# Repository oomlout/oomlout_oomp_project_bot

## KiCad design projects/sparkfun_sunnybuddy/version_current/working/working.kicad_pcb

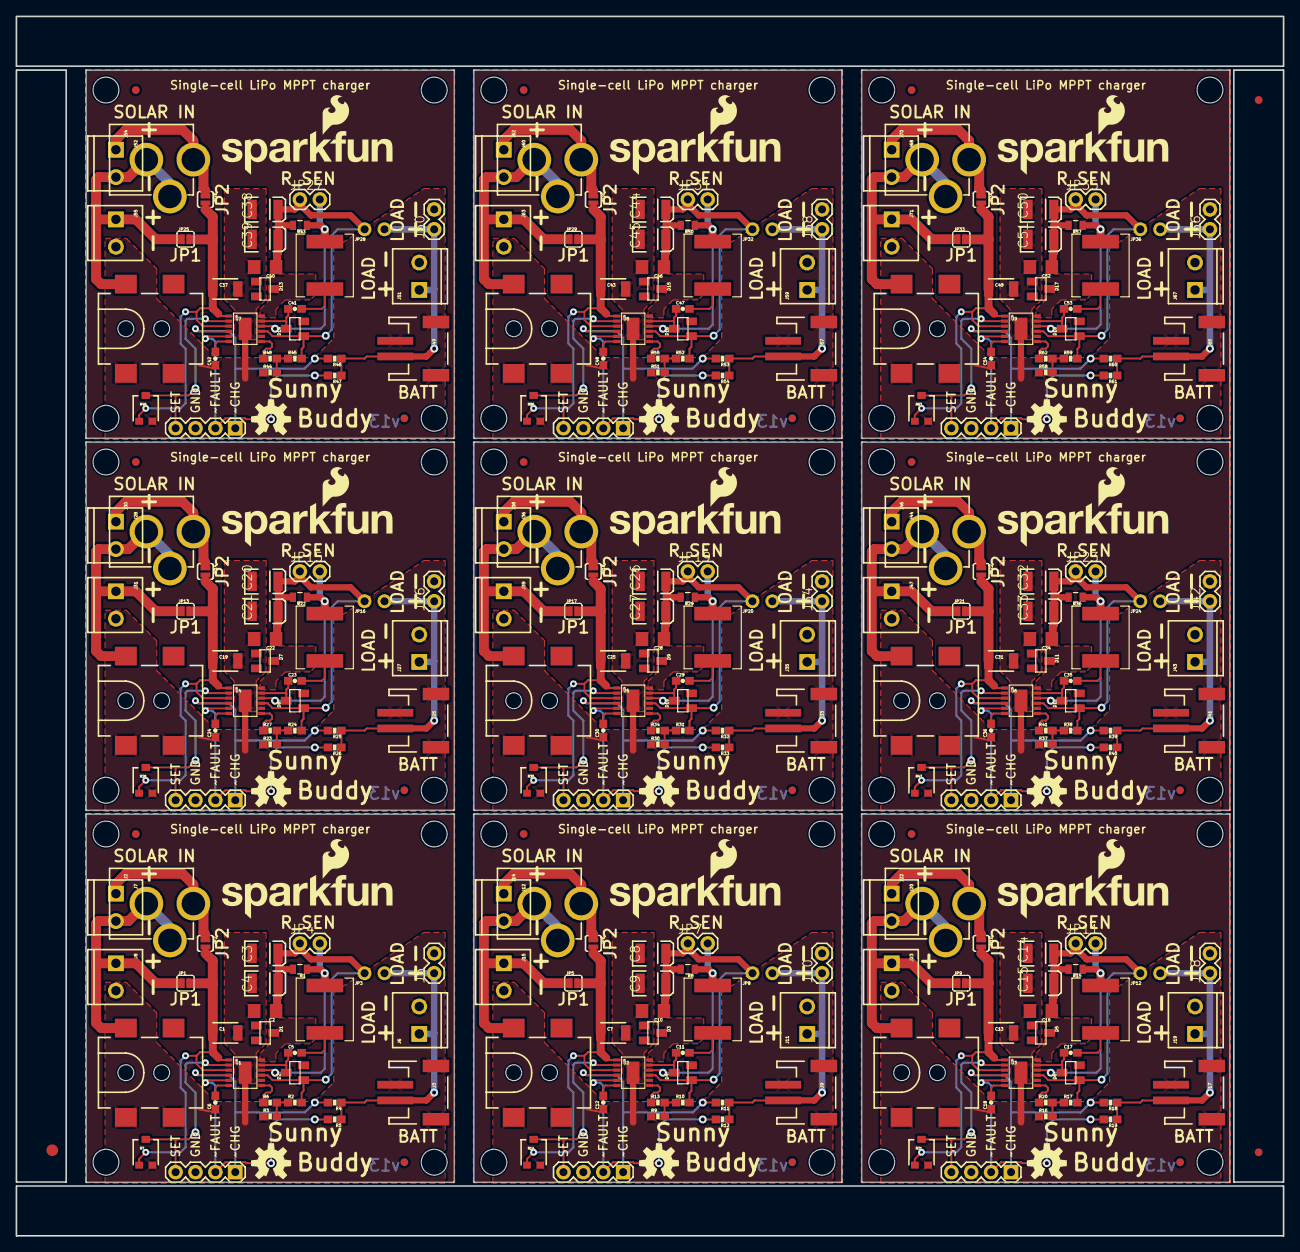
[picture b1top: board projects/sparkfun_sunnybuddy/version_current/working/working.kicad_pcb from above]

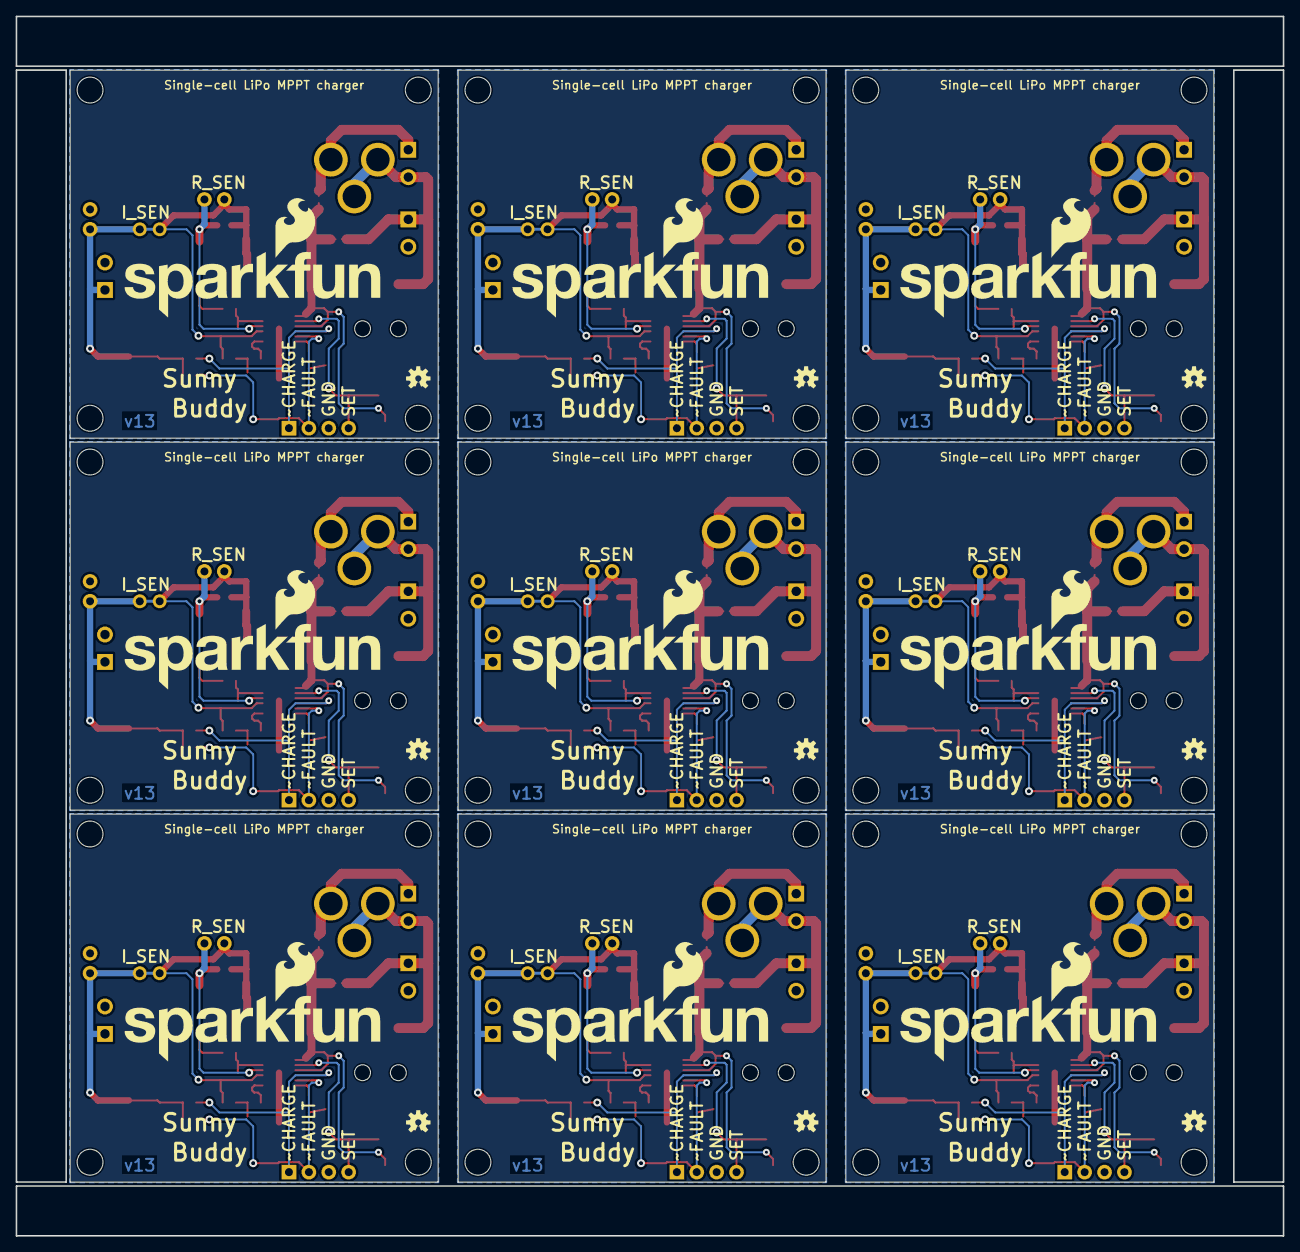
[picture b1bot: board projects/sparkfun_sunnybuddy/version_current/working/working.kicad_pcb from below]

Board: 4 copper layers, 161.8 x 155.7 mm, 354 parts (18 on the bottom side), 135 nets.

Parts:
C1, C7, C13, C19, C25, C31, C37, C43, C49: 10uF; 1210
C2, C10, C16, C22, C28, C34, C40, C46, C52: 10uF; 1206
C3, C4, C8, C9, C14, C15, C20, C21, C26, C27, C32, C33, C38, C39, C44, C45, C50, C51: 47uF; EIA3528
C5, C6, C11, C12, C17, C18, C23, C24, C29, C30, C35, C36, C41, C42, C47, C48, C53, C54: 1.0uF; 0603-CAP
D1, D2, D3, D4, D5, D6, D7, D8, D9, D10, D11, D12, D13, D14, D15, D16, D17, D18: ZLLS500; SOT23
E$1: FIDUCIAL-1.5X3
E$4, E$6: FIDUCIAL-1X2
FID1, FID2, FID3, FID4, FID5, FID6, FID7, FID8, FID9, FID10, FID11, FID12, FID13, FID14, FID15, FID16, FID17, FID18: FIDUCIAL1X2; FIDUCIAL-1X2
J1, J13, J21, J29, J37, J45, J53, J61, J69: 5.5x2.1mm Barrel; POWER_JACK_SMD
J2, J14, J22, J30, J38, J46, J54, J62, J70: POWER_JACKPTH; POWER_JACK_PTH
J3, J9, J17, J25, J33, J41, J49, J57, J65: JST-2-SMD
J4, J16, J24, J32, J40, J48, J56, J64, J72: 1X04
J5, J10, J18, J26, J34, J42, J50, J58, J66: M02PTH; 1X02
J6, J7, J8, J11, J12, J15, J19, J20, J23, J27, J28, J31, J35, J36, J39, J43, J44, J47, J51, J52, J55, J59, J60, J63, J67, J68, J71: M023.5MM; SCREWTERMINAL-3.5MM-2
JP1, JP5, JP9, JP13, JP17, JP21, JP25, JP29, JP33: SJ_2S
JP2, JP6, JP10, JP14, JP18, JP22, JP26, JP30, JP34: SJ_2S-NO
JP3, JP8, JP12, JP16, JP20, JP24, JP28, JP32, JP36: JUMPER-PTH-2-NC; PTH-JUMPER-NC_BOTTOM_NO_SILK
JP4, JP7, JP11, JP15, JP19, JP23, JP27, JP31, JP35: R_SEN; 1X02
L1, L2, L3, L4, L5, L6, L7, L8, L9: 68uH; CR75
LOGO1, LOGO5, LOGO9, LOGO13, LOGO17, LOGO21, LOGO25, LOGO29, LOGO33: SFE_LOGO_NAME_FLAME.2_INCH; SFE_LOGO_NAME_FLAME_.2
LOGO2, LOGO6, LOGO10, LOGO14, LOGO18, LOGO22, LOGO26, LOGO30, LOGO34: OSHW-LOGOM; OSHW-LOGO-M
LOGO3, LOGO7, LOGO11, LOGO15, LOGO19, LOGO23, LOGO27, LOGO31, LOGO35: OSHW-LOGOS; OSHW-LOGO-S
LOGO4, LOGO8, LOGO12, LOGO16, LOGO20, LOGO24, LOGO28, LOGO32, LOGO36: SFE_LOGO_NAME_FLAME.3_INCH; SFE_LOGO_NAME_FLAME_.3
R1, R8, R15, R22, R29, R36, R43, R50, R57: 0.22; 0805
R2, R10, R17, R24, R31, R38, R45, R52, R59: 47k; 0603-RES
R3, R6, R9, R13, R16, R20, R23, R27, R30, R34, R37, R41, R44, R48, R51, R55, R58, R62: 220k; 0603-RES
R4, R5, R11, R12, R18, R19, R25, R26, R32, R33, R39, R40, R46, R47, R53, R54, R60, R61: 10K; 0603-RES
R7, R14, R21, R28, R35, R42, R49, R56, R63: 10k; TRIMPOT-3MM
STANDOFF1, STANDOFF2, STANDOFF3, STANDOFF4, STANDOFF5, STANDOFF6, STANDOFF7, STANDOFF8, STANDOFF9, STANDOFF10, STANDOFF11, STANDOFF12, STANDOFF13, STANDOFF14, STANDOFF15, STANDOFF16, STANDOFF17, STANDOFF18, STANDOFF19, STANDOFF20, STANDOFF21, STANDOFF22, STANDOFF23, STANDOFF24, STANDOFF25, STANDOFF26, STANDOFF27, STANDOFF28, STANDOFF29, STANDOFF30, STANDOFF31, STANDOFF32, STANDOFF33, STANDOFF34, STANDOFF35, STANDOFF36: STAND-OFF
U1, U2, U3, U4, U5, U6, U7, U8, U9: LT3652; MSOP-12_GND

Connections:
BOOST: C5.1, D2.3, U1.11
BOOST1: R9.2, R10.1, R13.2
BOOST2: J24.1, R18.2, U3.4
BOOST3: J25.2, J26.1, J27.1, JP16.2, R25.1, R26.1
BOOST4: J36.1, J38.PWR, JP18.1
BOOST5: J48.4, R42.2, U6.2
BOOST6: C47.2, D15.3, L8.P$1, U8.12
BOOST7: C49.1, JP33.2, JP34.2, R63.1, U9.1, U9.3
FB: R2.1, R3.2, R6.2
FB1: J16.1, R11.2, U2.4
FB2: J17.2, J18.1, J19.1, JP12.2, R18.1, R19.1
FB3: J28.1, J30.PWR, JP14.1
FB4: J40.4, R35.2, U5.2
FB5: C41.2, D13.3, L7.P$1, U7.12
FB6: C43.1, JP29.2, JP30.2, R56.1, U8.1, U8.3
FB7: C53.1, D18.3, U9.11
GND: C1.2, C2.2, C3.C, C4.C, C6.1, D1.1, J1.GND, J1.P$4, J3.1, J3.NC1, J3.NC2, J4.3, J5.2, J6.2, J8.2, R3.1, R7.3, U1.13
GND1: C12.2, U2.6
GND3: J32.2, R26.2, U4.5
GND4: J36.2, J37.VIN0, J38.GND, J38.GNDBREAK, J39.1, JP17.1
GND5: R41.1, U6.7
GND6: C38.A, C39.A, C40.1, D14.1, JP27.1, JP28.1, R43.2, R45.2, U7.9
GND7: JP35.2, L9.P$2, R57.1, U9.10
unnamed: R6.1, U1.7
unnamed: J4.4, R7.2, U1.2
unnamed: C2.1, C3.A, C4.A, D2.1, JP3.1, JP4.1, R1.2, R2.2, U1.9
unnamed: JP7.2, L2.P$2, R8.1, U2.10
unnamed: R13.1, U2.7
unnamed: C8.A, C9.A, C10.1, D4.1, JP7.1, JP8.1, R8.2, R10.2, U2.9
unnamed: C17.2, D5.3, L3.P$1, U3.12
unnamed: J1.VIN0, J2.GND, J2.GNDBREAK, J7.2, J8.1, JP1.1
unnamed: JP11.2, L3.P$2, R15.1, U3.10
unnamed: C13.2, C14.C, C15.C, C16.2, C18.1, D5.1, J17.1, J17.NC1, J17.NC2, J18.2, J19.2, J21.GND, J21.P$4, J23.2, J24.3, R16.1, R21.3, U3.13
unnamed: C14.A, C15.A, C16.1, D6.1, JP11.1, JP12.1, R15.2, R17.2, U3.9
unnamed: JP15.2, L4.P$2, R22.1, U4.10
unnamed: C19.1, JP13.2, JP14.2, R28.1, U4.1, U4.3
unnamed: C19.2, C20.C, C21.C, C22.2, C24.1, D7.1, J25.1, J25.NC1, J25.NC2, J26.2, J27.2, J29.GND, J29.P$4, J31.2, J32.3, R23.1, R28.3, U4.13
unnamed: C24.2, U4.6
unnamed: JP19.2, L5.P$2, R29.1, U5.10
unnamed: C25.2, C26.C, C27.C, C28.2, C30.1, D9.1, J33.1, J33.NC1, J33.NC2, J34.2, J35.2, J37.GND, J37.P$4, J39.2, J40.3, R30.1, R35.3, U5.13
unnamed: C29.1, D10.3, U5.11
unnamed: C30.2, U5.6
unnamed: C31.2, C32.C, C33.C, C34.2, C36.1, D11.1, J41.1, J41.NC1, J41.NC2, J42.2, J43.2, J45.GND, J45.P$4, J47.2, J48.3, R37.1, R42.3, U6.13
unnamed: C36.2, U6.6
unnamed: R37.2, R38.1, R41.2
unnamed: J48.2, R40.2, U6.5
unnamed: C42.2, U7.6
unnamed: J56.1, R46.2, U7.4
unnamed: J56.2, R47.2, U7.5
unnamed: J52.2, J53.VIN0, J54.GND, J54.GNDBREAK, J55.1, JP25.1
unnamed: J64.2, R54.2, U8.5
unnamed: J57.2, J58.1, J59.1, JP32.2, R53.1, R54.1
unnamed: J60.2, J61.VIN0, J62.GND, J62.GNDBREAK, J63.1, JP29.1
unnamed: R55.1, U8.7
unnamed: J72.2, R61.2, U9.5
unnamed: J68.2, J69.VIN0, J70.GND, J70.GNDBREAK, J71.1, JP33.1
unnamed: J68.1, J70.PWR, JP34.1
unnamed: R62.1, U9.7
unnamed: C50.A, C51.A, C52.1, D18.1, JP35.1, JP36.1, R57.2, R59.2, U9.9
NTC1: J16.2, R12.2, U2.5
NTC2: J20.2, J21.VIN0, J22.GND, J22.GNDBREAK, J23.1, JP9.1
NTC3: R27.1, U4.7
NTC4: C26.A, C27.A, C28.1, D10.1, JP19.1, JP20.1, R29.2, R31.2, U5.9
NTC5: JP27.2, L7.P$2, R43.1, U7.10
NTC6: C43.2, C44.C, C45.C, C46.2, C48.1, D15.1, J57.1, J57.NC1, J57.NC2, J58.2, J59.2, J61.GND, J61.P$4, J63.2, J64.3, R51.1, R56.3, U8.13
NTC7: C54.2, U9.6
SENSE: JP4.2, L1.P$2, R1.1, U1.10
SENSE1: C7.2, C8.C, C9.C, C10.2, C12.1, D3.1, J9.1, J9.NC1, J9.NC2, J10.2, J11.2, J13.GND, J13.P$4, J15.2, J16.3, R9.1, R14.3, U2.13
SENSE2: C18.2, U3.6
SENSE4: J40.2, R33.2, U5.5
SENSE5: J44.2, J45.VIN0, J46.GND, J46.GNDBREAK, J47.1, JP21.1
SENSE6: R48.1, U7.7
SENSE7: C44.A, C45.A, C46.1, D16.1, JP31.1, JP32.1, R50.2, R52.2, U8.9
SET: C11.2, D3.3, L2.P$1, U2.12
SET1: C13.1, JP9.2, JP10.2, R21.1, U3.1, U3.3
SET2: C23.1, D8.3, U4.11
SET3: R30.2, R31.1, R34.2
SET4: J48.1, R39.2, U6.4
SET5: J49.2, J50.1, J51.1, JP28.2, R46.1, R47.1
SET6: J60.1, J62.PWR, JP30.1
SET7: J72.4, R63.2, U9.2
SFSASDF: J2.PWR, J7.1, JP2.1
SFSASDF1: J16.4, R14.2, U2.2
SFSASDF2: C23.2, D7.3, L4.P$1, U4.12
SFSASDF3: C25.1, JP17.2, JP18.2, R35.1, U5.1, U5.3
SFSASDF4: C35.1, D12.3, U6.11
SFSASDF5: R44.2, R45.1, R48.2
SFSASDF6: J64.1, R53.2, U8.4
SFSASDF7: J65.2, J66.1, J67.1, JP36.2, R60.1, R61.1
SW: C5.2, D1.3, L1.P$1, U1.12
SW1: C7.1, JP5.2, JP6.2, R14.1, U2.1, U2.3
SW2: C17.1, D6.3, U3.11
SW3: R23.2, R24.1, R27.2
SW4: J40.1, R32.2, U5.4
SW5: J41.2, J42.1, J43.1, JP24.2, R39.1, R40.1
SW6: J52.1, J54.PWR, JP26.1
SW7: J64.4, R56.2, U8.2
TIMER: C6.2, U1.6
TIMER2: J24.2, R19.2, U3.5
TIMER3: J28.2, J29.VIN0, J30.GND, J30.GNDBREAK, J31.1, JP13.1
TIMER4: R34.1, U5.7
TIMER5: C32.A, C33.A, C34.1, D12.1, JP23.1, JP24.1, R36.2, R38.2, U6.9
TIMER6: JP31.2, L8.P$2, R50.1, U8.10
TIMER7: C49.2, C50.C, C51.C, C52.2, C54.1, D17.1, J65.1, J65.NC1, J65.NC2, J66.2, J67.2, J69.GND, J69.P$4, J71.2, J72.3, R58.1, R63.3, U9.13
VIN: C1.1, JP1.2, JP2.2, R7.1, U1.1, U1.3
VIN1: C11.1, D4.3, U2.11
VIN2: R16.2, R17.1, R20.2
VIN3: J32.1, R25.2, U4.4
VIN4: J33.2, J34.1, J35.1, JP20.2, R32.1, R33.1
VIN5: J44.1, J46.PWR, JP22.1
VIN6: J56.4, R49.2, U7.2
VIN7: C53.2, D17.3, L9.P$1, U9.12
V_BATT: J3.2, J5.1, J6.1, JP3.2, R4.1, R5.1
V_BATT1: J12.1, J14.PWR, JP6.1
V_BATT2: J24.4, R21.2, U3.2
V_BATT3: C29.2, D9.3, L5.P$1, U5.12
V_BATT4: C31.1, JP21.2, JP22.2, R42.1, U6.1, U6.3
V_BATT5: C41.1, D14.3, U7.11
V_BATT6: R51.2, R52.1, R55.2
V_BATT7: J72.1, R60.2, U9.4
~CHRG1: J9.2, J10.1, J11.1, JP8.2, R11.1, R12.1
~CHRG2: J20.1, J22.PWR, JP10.1
~CHRG3: J32.4, R28.2, U4.2
~CHRG4: C35.2, D11.3, L6.P$1, U6.12
~CHRG5: C37.1, JP25.2, JP26.2, R49.1, U7.1, U7.3
~CHRG6: C47.1, D16.3, U8.11
~CHRG7: R58.2, R59.1, R62.2
~CHRG: J4.1, R4.2, U1.4
~FAULT1: J12.2, J13.VIN0, J14.GND, J14.GNDBREAK, J15.1, JP5.1
~FAULT2: R20.1, U3.7
~FAULT3: C20.A, C21.A, C22.1, D8.1, JP15.1, JP16.1, R22.2, R24.2, U4.9
~FAULT4: JP23.2, L6.P$2, R36.1, U6.10
~FAULT5: C37.2, C38.C, C39.C, C40.2, C42.1, D13.1, J49.1, J49.NC1, J49.NC2, J50.2, J51.2, J53.GND, J53.P$4, J55.2, J56.3, R44.1, R49.3, U7.13
~FAULT6: C48.2, U8.6
~FAULT: J4.2, R5.2, U1.5

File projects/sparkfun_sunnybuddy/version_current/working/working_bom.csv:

"Id";"Designator";"Footprint";"Quantity";"Designation";"Supplier and ref";
1;"E$6,E$4";"FIDUCIAL-1X2";2;"";;;
2;"J70,J30,J2,J62,J54,J22,J14,J46,J38";"POWER_JACK_PTH";9;"POWER_JACKPTH";;;
3;"L9,L7,L1,L3,L6,L4,L5,L2,L8";"CR75";9;"68uH";;;
4;"FID17,FID4,FID18,FID3,FID13,FID9,FID8,FID12,FID16,FID7,FID11,FID10,FID2,FID1,FID15,FID5,FID14,FID6";"FIDUCIAL-1X2";18;"FIDUCIAL1X2";;;
5;"C42,C18,C36,C48,C24,C53,C54,C11,C23,C12,C29,C6,C41,C17,C30,C47,C5,C35";"0603-CAP";18;"1.0uF";;;
6;"JP8,JP16,JP20,JP28,JP32,JP12,JP36,JP24,JP3";"PTH-JUMPER-NC_BOTTOM_NO_SILK";9;"JUMPER-PTH-2-NC";;;
7;"STANDOFF7,STANDOFF11,STANDOFF18,STANDOFF17,STANDOFF4,STANDOFF29,STANDOFF23,STANDOFF33,STANDOFF3,STANDOFF35,STANDOFF16,STANDOFF21,STANDOFF19,STANDOFF13,STANDOFF2,STANDOFF27,STANDOFF12,STANDOFF31,STANDOFF1,STANDOFF15,STANDOFF24,STANDOFF30,STANDOFF14,STANDOFF8,STANDOFF34,STANDOFF28,STANDOFF25,STANDOFF22,STANDOFF5,STANDOFF32,STANDOFF26,STANDOFF10,STANDOFF6,STANDOFF36,STANDOFF20,STANDOFF9";"STAND-OFF";36;"STAND-OFF";;;
8;"J69,J1,J21,J45,J13,J37,J53,J61,J29";"POWER_JACK_SMD";9;"5.5x2.1mm Barrel";;;
9;"C9,C4,C14,C39,C20,C32,C45,C44,C26,C8,C3,C33,C27,C50,C51,C21,C38,C15";"EIA3528";18;"47uF";;;
10;"C34,C28,C22,C16,C52,C40,C2,C10,C46";"1206";9;"10uF";;;
11;"R49,R35,R7,R42,R56,R28,R21,R14,R63";"TRIMPOT-3MM";9;"10k";;;
12;"LOGO30,LOGO34,LOGO18,LOGO26,LOGO14,LOGO2,LOGO6,LOGO10,LOGO22";"OSHW-LOGO-M";9;"OSHW-LOGOM";;;
13;"R41,R20,R13,R62,R37,R55,R6,R44,R51,R9,R30,R27,R58,R3,R48,R34,R16,R23";"0603-RES";18;"220k";;;
14;"U7,U3,U9,U6,U2,U5,U4,U8,U1";"MSOP-12_GND";9;"LT3652";;;
15;"J63,J27,J71,J20,J15,J11,J47,J8,J51,J52,J7,J43,J12,J59,J67,J39,J36,J6,J44,J55,J23,J60,J28,J31,J68,J19,J35";"SCREWTERMINAL-3.5MM-2";27;"M023.5MM";;;
16;"J10,J26,J18,J5,J58,J34,J66,J42,J50";"1X02";9;"M02PTH";;;
17;"C43,C19,C13,C1,C25,C7,C31,C49,C37";"1210";9;"10uF";;;
18;"LOGO17,LOGO5,LOGO1,LOGO9,LOGO21,LOGO25,LOGO13,LOGO29,LOGO33";"SFE_LOGO_NAME_FLAME_.2";9;"SFE_LOGO_NAME_FLAME.2_INCH";;;
19;"J56,J24,J64,J72,J16,J4,J40,J32,J48";"1X04";9;"";;;
20;"R52,R24,R38,R31,R59,R17,R45,R10,R2";"0603-RES";9;"47k";;;
21;"D7,D8,D5,D17,D4,D14,D18,D6,D2,D10,D13,D15,D9,D11,D3,D1,D12,D16";"SOT23";18;"ZLLS500";;;
22;"JP30,JP34,JP26,JP18,JP14,JP2,JP10,JP6,JP22";"SJ_2S-NO";9;"";;;
23;"R18,R40,R39,R61,R32,R26,R4,R5,R53,R19,R60,R25,R11,R33,R46,R54,R47,R12";"0603-RES";18;"10K";;;
24;"JP21,JP5,JP1,JP9,JP13,JP33,JP17,JP25,JP29";"SJ_2S";9;"";;;
25;"J41,J9,J25,J49,J3,J57,J65,J33,J17";"JST-2-SMD";9;"";;;
26;"R50,R43,R1,R29,R8,R22,R36,R15,R57";"0805";9;"0.22";;;
27;"JP23,JP19,JP7,JP15,JP35,JP11,JP27,JP31,JP4";"1X02";9;"R_SEN";;;
28;"E$1";"FIDUCIAL-1.5X3";1;"";;;
29;"LOGO36,LOGO20,LOGO16,LOGO32,LOGO4,LOGO8,LOGO12,LOGO28,LOGO24";"SFE_LOGO_NAME_FLAME_.3";9;"SFE_LOGO_NAME_FLAME.3_INCH";;;
30;"LOGO15,LOGO7,LOGO11,LOGO27,LOGO3,LOGO35,LOGO19,LOGO31,LOGO23";"OSHW-LOGO-S";9;"OSHW-LOGOS";;;

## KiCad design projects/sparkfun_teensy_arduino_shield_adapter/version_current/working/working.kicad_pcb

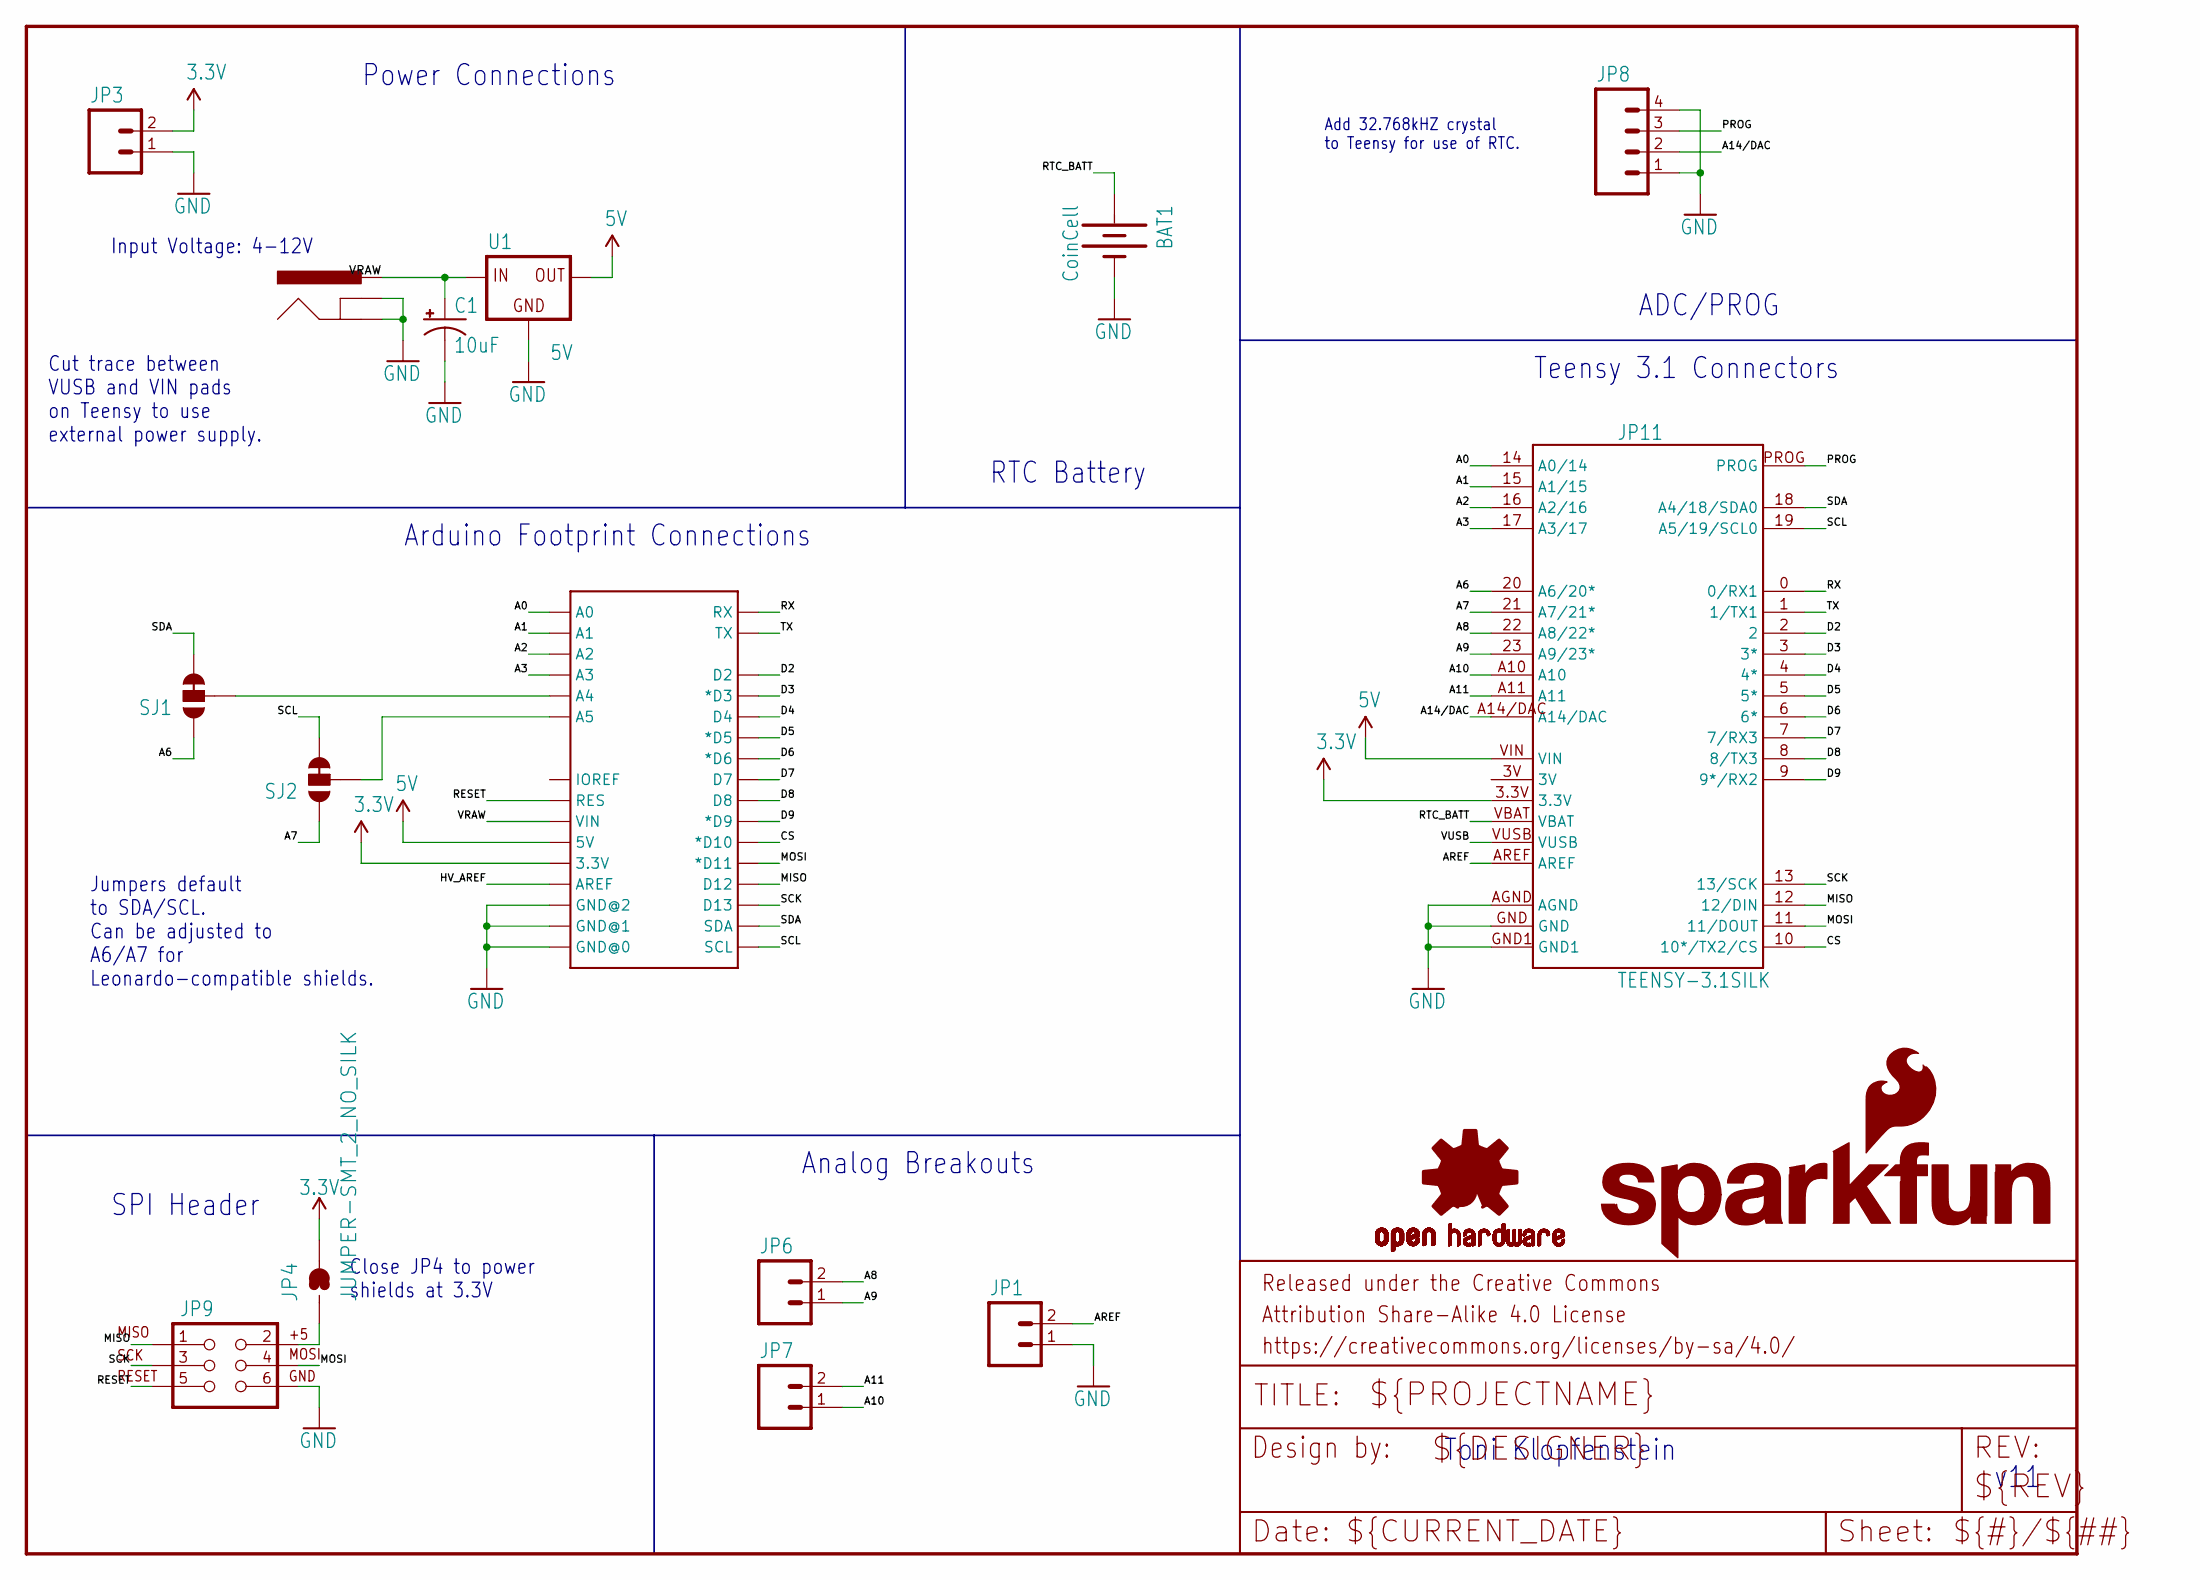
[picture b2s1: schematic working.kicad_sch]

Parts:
BAT1: CoinCell; BATTCON_12MM_PTH
C1: 10uF; CPOL-RADIAL-10UF-25V
FRAME1: FRAME-LETTER; CREATIVE_COMMONS
JP1, JP6, JP7: M02PTH; 1X02
JP2: POWER_JACKPTH_LOCK; POWER_JACK_PTH_LOCK
JP3: JST2; JST-2-PTH
JP4: JUMPER-SMT_2_NO_SILK; SMT-JUMPER_2_NO_SILK
JP8: M04PTH; 1X04
JP9: AVR_SPI_PRG_6PTH; 2X3
JP10: ARDUINO_R3_SHIELDUNO_R3_SHIELD_HOLES; UNO_R3_SHIELD_HOLES
JP11: TEENSY-3.1SILK; TEENSY-3.1
LOGO1: SFE_LOGO_NAME_FLAME.1_INCH; SFE_LOGO_NAME_FLAME_.1
LOGO2: OSHW-LOGOM; OSHW-LOGO-M
SJ1, SJ2: JUMPER-PAD-3-2OF3_NC_BY_TRACE_SMALL; PAD-JUMPER-3-2OF3_NC_BY_TRACE_YES_SILK_FULL_BOX
U1: 5V; TO-220-ALT

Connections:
3.3V: JP3.2, JP4.2, JP10.3.3V, JP11.3.3V
5V: JP10.5V, JP11.VIN, U1.OUT
A0: JP10.A0, JP11.14 (A0/14)
A1: JP10.A1, JP11.15 (A1/15)
A2: JP10.A2, JP11.16 (A2/16)
A3: JP10.A3, JP11.17 (A3/17)
A4: JP10.A4, SJ1.2
A5: JP10.A5, SJ2.2
A6: JP11.20 (A6/20*), SJ1.1
A7: JP11.21 (A7/21*), SJ2.1
A8: JP6.2, JP11.22 (A8/22*)
A9: JP6.1, JP11.23 (A9/23*)
A10: JP7.1, JP11.A10
A11: JP7.2, JP11.A11
A14/DAC: JP8.2, JP11.A14/DAC
AREF: JP1.2, JP11.AREF
CS: JP10.D10 (*D10), JP11.10 (10*/TX2/CS)
D2: JP10.D2, JP11.2
D3: JP10.D3 (*D3), JP11.3 (3*)
D4: JP10.D4, JP11.4 (4*)
D5: JP10.D5 (*D5), JP11.5 (5*)
D6: JP10.D6 (*D6), JP11.6 (6*)
D7: JP10.D7, JP11.7 (7/RX3)
D8: JP10.D8, JP11.8 (8/TX3)
D9: JP10.D9 (*D9), JP11.9 (9*/RX2)
GND: BAT1.GND (-), C1.2 (-), JP1.1, JP2.GND, JP2.GNDBREAK, JP3.1, JP8.1, JP8.4, JP9.6, JP10.GND@0, JP10.GND@1, JP10.GND@2, JP11.AGND, JP11.GND, JP11.GND1, U1.GND
HV_AREF: JP10.AREF
MISO: JP9.1, JP10.D12, JP11.12 (12/DIN)
MOSI: JP9.4, JP10.D11 (*D11), JP11.11 (11/DOUT)
unnamed: JP4.1, JP9.2
PROG: JP8.3, JP11.PROG
RESET: JP9.5, JP10.RES
RTC_BATT: BAT1.VCC@1 (+), JP11.VBAT
RX: JP10.RX, JP11.0 (0/RX1)
SCK: JP9.3, JP10.D13, JP11.13 (13/SCK)
SCL: JP10.SCL, JP11.19 (A5/19/SCL0), SJ2.3
SDA: JP10.SDA, JP11.18 (A4/18/SDA0), SJ1.3
TX: JP10.TX, JP11.1 (1/TX1)
VRAW: C1.1 (+), JP2.PWR, JP10.VIN, U1.IN
VUSB: JP11.VUSB

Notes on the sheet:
Analog Breakouts
Teensy 3.1 Connectors
RTC Battery
ADC/PROG
Arduino Footprint Connections
Power Connections
Cut trace between VUSB and VIN pads on Teensy to use external power supply.
Jumpers default to SDA/SCL. Can be adjusted to A6/A7 for Leonardo-compatible shields.
SPI Header
Toni Klopfenstein
Input Voltage: 4-12V
Add 32.768kHZ crystal to Teensy for use of RTC.
Close JP4 to power shields at 3.3V
v11

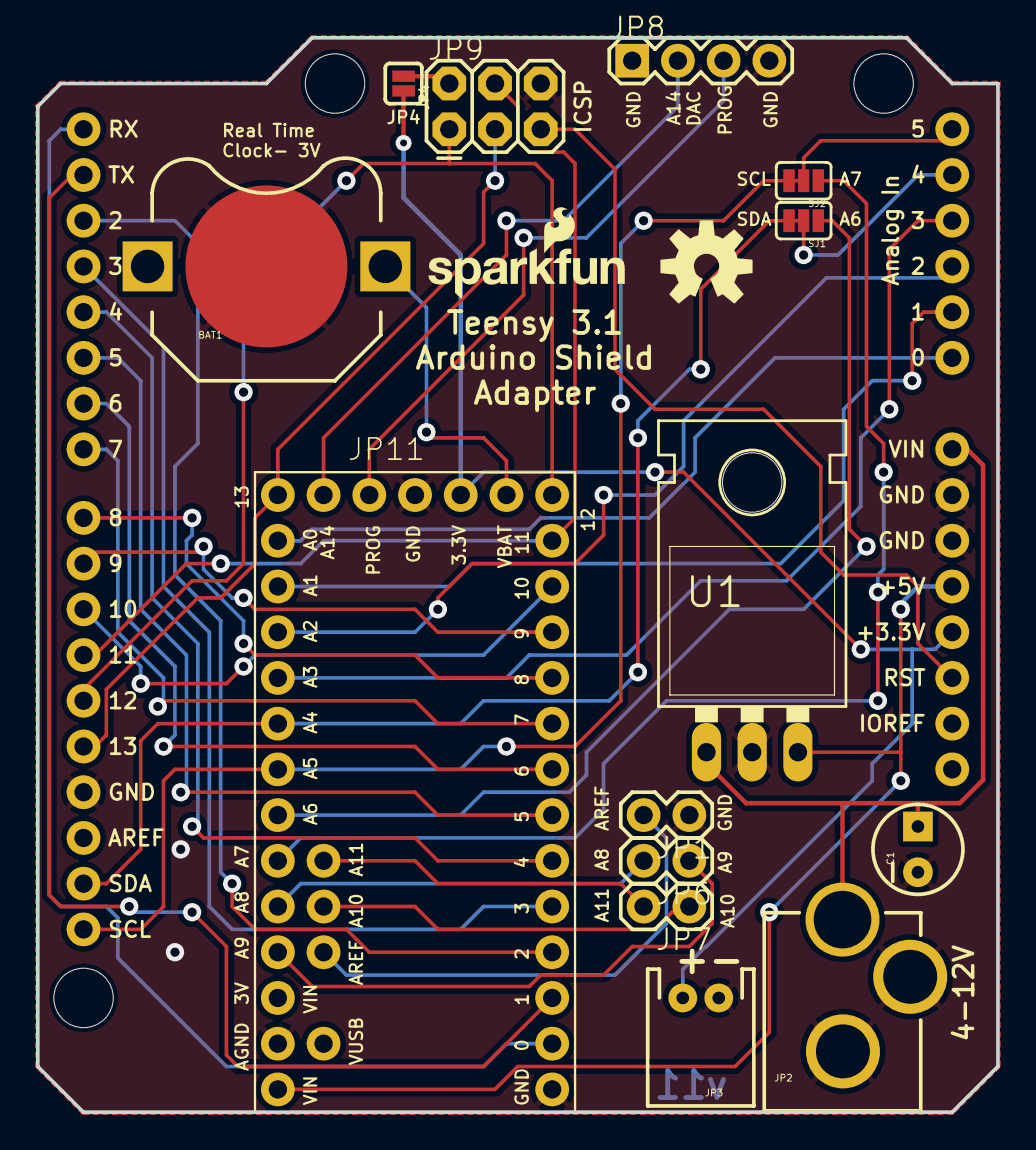
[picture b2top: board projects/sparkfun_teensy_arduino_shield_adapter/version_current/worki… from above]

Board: 2 copper layers, 53.3 x 59.7 mm, 18 parts (0 on the bottom side), 38 nets.

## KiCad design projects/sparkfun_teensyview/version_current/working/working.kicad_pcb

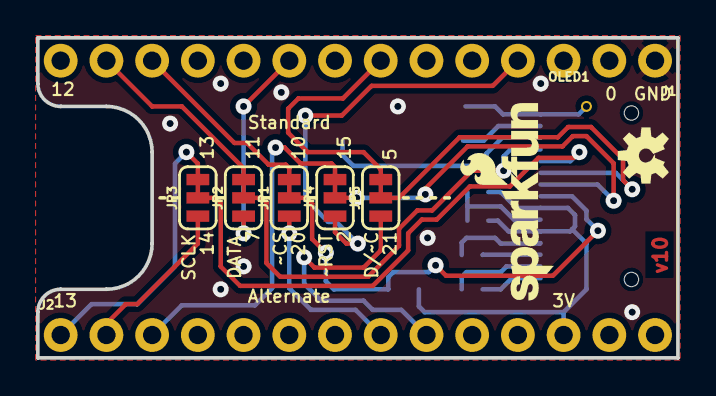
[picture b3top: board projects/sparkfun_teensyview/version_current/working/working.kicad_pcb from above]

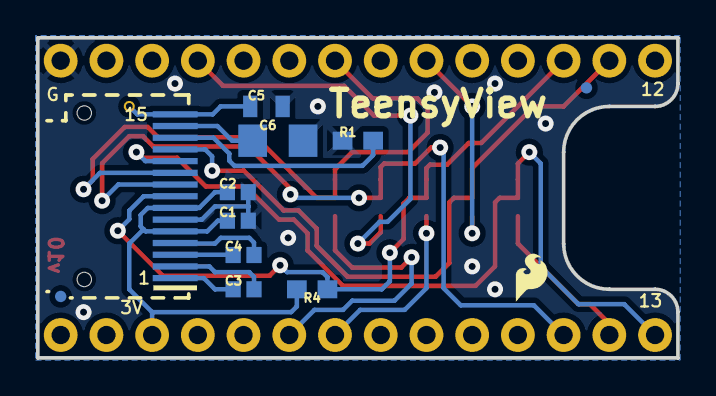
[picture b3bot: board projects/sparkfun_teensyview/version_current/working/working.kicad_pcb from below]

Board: 2 copper layers, 35.6 x 17.8 mm, 23 parts (12 on the bottom side), 24 nets.

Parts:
C1, C2, C3, C4: 1.0uF; 0402
C5: 2.2uF; 0805
C6: 4.7uF; 1206
FD1, FD2: FIDUCIALUFIDUCIAL; FIDUCIAL-MICRO
FRAME1: FRAME-LETTER; CREATIVE_COMMONS
J1, J2: DNP; 1X14_NO_SILK
JP1, JP2, JP3, JP4, JP5: JUMPER-SMT_3_1-NC_TRACE_SILK; SMT-JUMPER_3_1-NC_TRACE_SILK
LOGO1: SFE_LOGO_FLAME.1_INCH; SFE_LOGO_FLAME_.1
LOGO2: OSHW-LOGOS; OSHW-LOGO-S
LOGO3: SFE_LOGO_NAME_FLAME.1_INCH; SFE_LOGO_NAME_FLAME_.1
OLED1: 32x128 OLED; OLED-UG-2832TSWGG01-REAR
R1: 390k; 0603
R4: 4.7k; 0603
TP1: TEST-POINTTP_15TH_THRU; TP_15TH

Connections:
D/~C: JP5.2, OLED1.10
GND: C1.2, C2.2, C5.2, C6.2, J1.1, OLED1.6, R1.1
unnamed: J1.12, JP1.3
unnamed: J2.8, JP1.1
unnamed: C4.2, OLED1.4
unnamed: C4.1, OLED1.3
unnamed: C3.2, OLED1.2
unnamed: C3.1, OLED1.1
unnamed: OLED1.13, R1.2
unnamed: C6.1, OLED1.14
unnamed: C5.1, OLED1.15, TP1.P$1
unnamed: J2.1, JP3.3
unnamed: J2.2, JP3.1
unnamed: J1.13, JP2.3
unnamed: J1.9, JP2.1
unnamed: J2.3, JP4.3
unnamed: J1.4, JP4.1
unnamed: J1.7, JP5.3
unnamed: J2.9, JP5.1
SCLK: JP3.2, OLED1.11
SDIN: JP2.2, OLED1.12
VCC: C1.1, C2.1, J2.12, OLED1.5, OLED1.7, R4.2
~CS: JP1.2, OLED1.8, R4.1
~RESET: JP4.2, OLED1.9

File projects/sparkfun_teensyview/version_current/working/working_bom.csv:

"Id";"Designator";"Footprint";"Quantity";"Designation";"Supplier and ref";
1;"LOGO2";"OSHW-LOGO-S";1;"OSHW-LOGOS";;;
2;"J1,J2";"1X14_NO_SILK";2;"DNP";;;
3;"FRAME1";"CREATIVE_COMMONS";1;"FRAME-LETTER";;;
4;"JP4,JP3,JP2,JP1,JP5";"SMT-JUMPER_3_1-NC_TRACE_SILK";5;"JUMPER-SMT_3_1-NC_TRACE_SILK";;;
5;"LOGO3";"SFE_LOGO_NAME_FLAME_.1";1;"SFE_LOGO_NAME_FLAME.1_INCH";;;
6;"OLED1";"OLED-UG-2832TSWGG01-REAR";1;"32x128 OLED";;;
7;"R1";"0603";1;"390k";;;
8;"TP1";"TP_15TH";1;"TEST-POINTTP_15TH_THRU";;;
9;"FD1,FD2";"FIDUCIAL-MICRO";2;"FIDUCIALUFIDUCIAL";;;
10;"C2,C3,C1,C4";"0402";4;"1.0uF";;;
11;"R4";"0603";1;"4.7k";;;
12;"LOGO1";"SFE_LOGO_FLAME_.1";1;"SFE_LOGO_FLAME.1_INCH";;;
13;"C5";"0805";1;"2.2uF";;;
14;"C6";"1206";1;"4.7uF";;;

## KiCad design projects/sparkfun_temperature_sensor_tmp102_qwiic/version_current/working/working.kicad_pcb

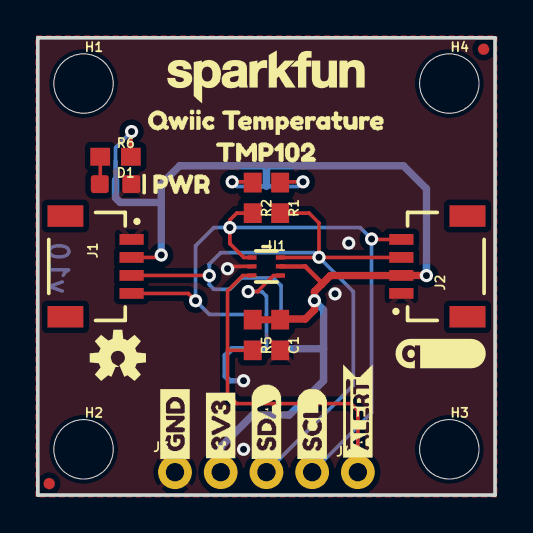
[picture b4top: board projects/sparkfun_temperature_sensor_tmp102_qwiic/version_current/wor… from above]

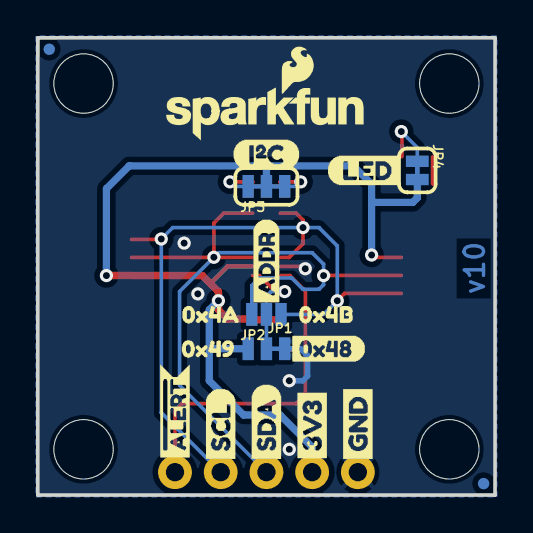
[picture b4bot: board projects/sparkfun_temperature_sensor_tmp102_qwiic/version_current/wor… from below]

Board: 2 copper layers, 25.4 x 25.4 mm, 48 parts (19 on the bottom side), 10 nets.

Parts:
C1: 0.1uF; 0603
D1: RED; LED-0603
FD1, FD2, FD3, FD4: FIDUCIALUFIDUCIAL; FIDUCIAL-MICRO
FRAME1: FRAME-LETTER; CREATIVE_COMMONS
H1, H2, H3, H4: STAND-OFF
J1, J2: QWIIC; JST04_1MM_RA
J3: PTH; 1X04_NO_SILK
J4: 1X01_NO_SILK
JP1: SMT-JUMPER_3_1-NC_TRACE_NO-SILK
JP2: SMT-JUMPER_3_NO_NO-SILK
JP3: I2C; SMT-JUMPER_3_2-NC_TRACE_SILK
JP4: PWR; SMT-JUMPER_2_NC_TRACE_SILK
LOGO1: SFE_LOGO_NAME.1_INCH; SFE_LOGO_NAME_.1
LOGO2: QWIIC_LOGO_5MM; QWIIC_5MM
LOGO3: OSHW-LOGOS; OSHW-LOGO-S
R1, R2: 4.7k; 0603
R5: 10k; 0603
R6: 1k; 0603
U1: TMP102; SOT563
U$1, U$10: #ALERT8
U$2, U$9: SCL7
U$3, U$8: SDA6
U$4, U$7: 3V35
U$5, U$6: GND4
U$11: ADDR0
U$12: 0X481
U$13: 0X494
U$14: 0X4A2
U$15: 0X4B3
U$16: I#C0
U$17: LED0
U$18: QWIIC_TEMPERATURE0
U$19: TMP1022
U$20: PWR1
U$21: SFE_LOGO_NAME_FLAME_.1

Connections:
3.3V: C1.1, J1.2, J2.2, J3.2, JP1.1, JP3.2, JP4.2, R5.1, U1.5
ADDR: JP1.2, JP2.2, U1.4
GND: C1.2, D1.C, J1.1, J2.1, J3.1, JP1.3, U1.2
unnamed: JP3.3, R1.1
unnamed: JP3.1, R2.1
unnamed: D1.A, R6.1
unnamed: JP4.1, R6.2
SCL: J1.4, J2.4, J3.4, JP2.1, R2.2, U1.1
SDA: J1.3, J2.3, J3.3, JP2.3, R1.2, U1.6
~ALERT: J4.1, R5.2, U1.3

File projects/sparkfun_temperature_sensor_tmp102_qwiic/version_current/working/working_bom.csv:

"Id";"Designator";"Footprint";"Quantity";"Designation";"Supplier and ref";
1;"U$5,U$6";"GND4";2;"";;;
2;"FD1,FD3,FD4,FD2";"FIDUCIAL-MICRO";4;"FIDUCIALUFIDUCIAL";;;
3;"H4,H1,H2,H3";"STAND-OFF";4;"STAND-OFF";;;
4;"J3";"1X04_NO_SILK";1;"PTH";;;
5;"FRAME1";"CREATIVE_COMMONS";1;"FRAME-LETTER";;;
6;"U$3,U$8";"SDA6";2;"";;;
7;"U$1,U$10";"#ALERT8";2;"";;;
8;"D1";"LED-0603";1;"RED";;;
9;"LOGO3";"OSHW-LOGO-S";1;"OSHW-LOGOS";;;
10;"C1";"0603";1;"0.1uF";;;
11;"J2,J1";"JST04_1MM_RA";2;"QWIIC";;;
12;"U$19";"TMP1022";1;"";;;
13;"LOGO1";"SFE_LOGO_NAME_.1";1;"SFE_LOGO_NAME.1_INCH";;;
14;"U$18";"QWIIC_TEMPERATURE0";1;"";;;
15;"R1,R2";"0603";2;"4.7k";;;
16;"R5";"0603";1;"10k";;;
17;"LOGO2";"QWIIC_5MM";1;"QWIIC_LOGO_5MM";;;
18;"U1";"SOT563";1;"TMP102";;;
19;"J4";"1X01_NO_SILK";1;"";;;
20;"R6";"0603";1;"1k";;;
21;"U$20";"PWR1";1;"";;;
22;"U$2,U$9";"SCL7";2;"";;;
23;"U$4,U$7";"3V35";2;"";;;
24;"U$13";"0X494";1;"";;;
25;"JP4";"SMT-JUMPER_2_NC_TRACE_SILK";1;"PWR";;;
26;"U$16";"I#C0";1;"";;;
27;"U$15";"0X4B3";1;"";;;
28;"U$11";"ADDR0";1;"";;;
29;"U$21";"SFE_LOGO_NAME_FLAME_.1";1;"";;;
30;"JP2";"SMT-JUMPER_3_NO_NO-SILK";1;"";;;
31;"U$12";"0X481";1;"";;;
32;"JP3";"SMT-JUMPER_3_2-NC_TRACE_SILK";1;"I2C";;;
33;"U$17";"LED0";1;"";;;
34;"U$14";"0X4A2";1;"";;;
35;"JP1";"SMT-JUMPER_3_1-NC_TRACE_NO-SILK";1;"";;;

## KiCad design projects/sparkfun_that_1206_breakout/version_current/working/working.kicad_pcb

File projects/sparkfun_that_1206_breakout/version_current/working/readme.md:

# THAT_1206_Breakout by sparkfun  
This is a harvested standardized copy of a project from github.  
The original project can be found at:  
https://github.com/sparkfun/THAT_1206_Breakout  
Please consult that link for additional, details, files, and license information.  
Note: It was auto harvested and if the original repo had more than one board file or anything out of the ordinary the files here are likely not representative.

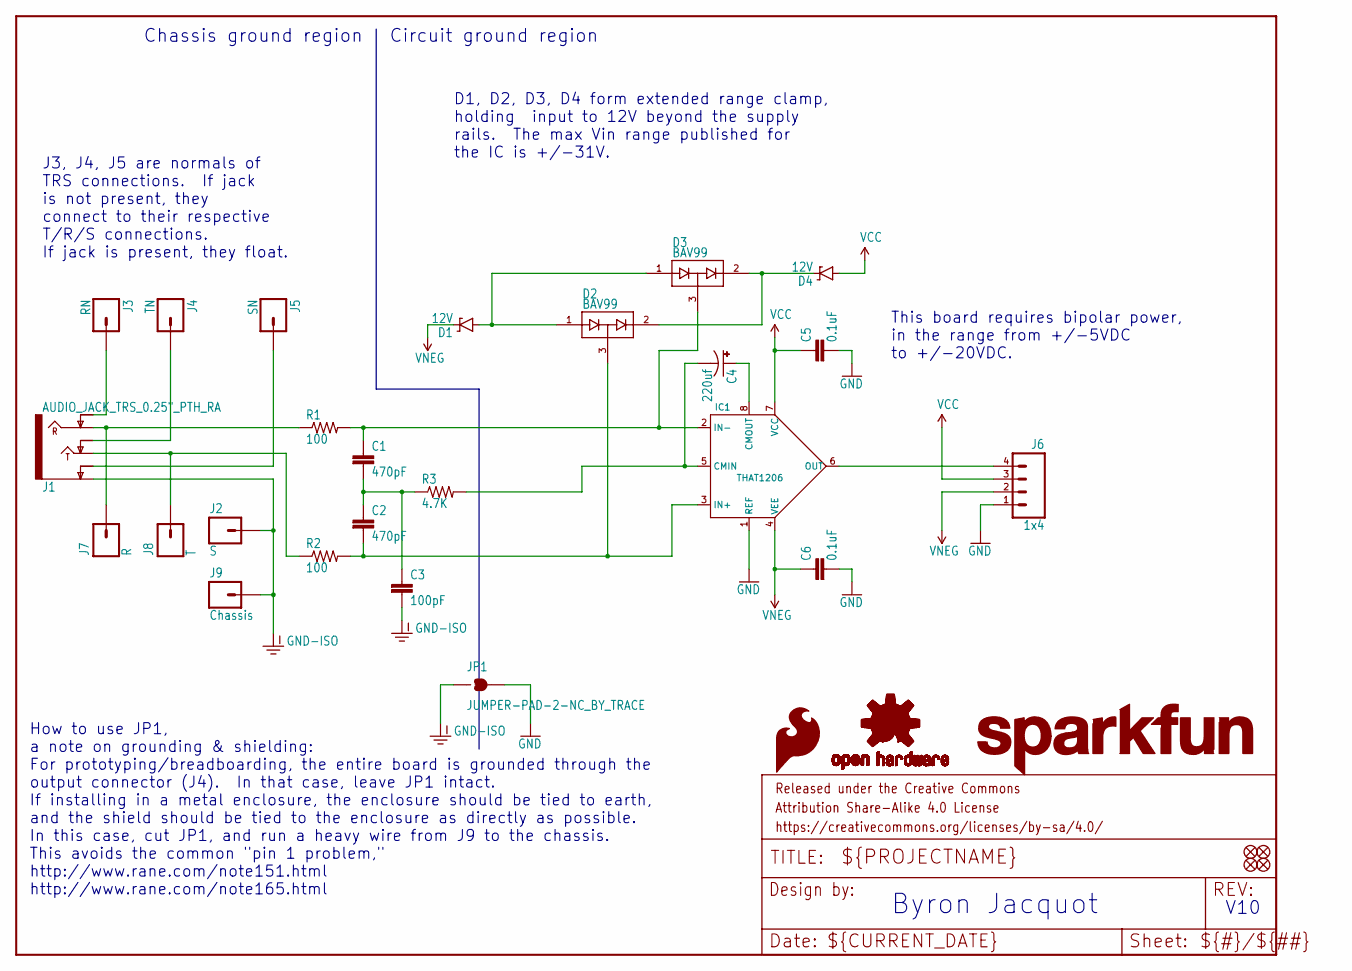
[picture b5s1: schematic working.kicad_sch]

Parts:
C1, C2: 470pF; 0603-CAP
C3: 100pF; 0603-CAP
C4: 220uf; PANASONIC_D
C5, C6: 0.1uF; 0603-CAP
D1, D4: 12V; SOD-323
D2, D3: BAV99; SOT23-3
FD1, FD2, FD3, FD4: FIDUCIALUFIDUCIAL; MICRO-FIDUCIAL
FRAME1: FRAME-LETTER; CREATIVE_COMMONS
IC1: THAT1206; SO08
J1: AUDIO_JACK_TRS_0.25"_PTH_RA; AUDIO_JACK_0.25__TRS_PTH_RA
J2: S; 1X01_NO_SILK
J3: RN; 1X01_NO_SILK
J4: TN; 1X01_NO_SILK
J5: SN; 1X01_NO_SILK
J6: 1x4; 1X04_NO_SILK_ALL_ROUND
J7: R; 1X01_NO_SILK
J8: T; 1X01_NO_SILK
J9: Chassis; 1X01_NO_SILK
JP1: JUMPER-PAD-2-NC_BY_TRACE; PAD-JUMPER-2-NC_BY_TRACE_YES_SILK
LOGO2: SFE_LOGO_FLAME.2_INCH; SFE_LOGO_FLAME_.2
LOGO3, LOGO4: OSHW-LOGOS; OSHW-LOGO-S
LOGO5: SFE_LOGO_NAME.1_INCH; SFE_LOGO_NAME_.1
R1, R2: 100; 0603-RES
R3: 4.7K; 0603-RES

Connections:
GND: C5.2, C6.2, IC1.1 (REF), J6.1, JP1.2
GND-ISO: C3.2, J1.SLEEVE (EARTH), J2.1, J9.1, JP1.1
unnamed: J1.RING, J7.1, R1.1
unnamed: C1.1, D3.3 (COM), IC1.2 (IN-), R1.2
unnamed: J1.TIP, J8.1, R2.1
unnamed: C2.2, D2.3 (COM), IC1.3 (IN+), R2.2
unnamed: C1.2, C2.1, C3.1, R3.1
unnamed: C4.-, IC1.5 (CMIN), R3.2
unnamed: C4.+, IC1.8 (CMOUT)
unnamed: J1.SLEEVE-NORM (EARTH-NORM), J5.1
unnamed: J1.TIP-NORM, J4.1
unnamed: J1.RING-NORM, J3.1
unnamed: D1.A, D2.1 (A1), D3.1 (A1)
unnamed: D2.2 (C2), D3.2 (C2), D4.C
RCV: IC1.6 (OUT), J6.4
VCC: C5.1, D4.A, IC1.7 (VCC), J6.3
VNEG: C6.1, D1.C, IC1.4 (VEE), J6.2

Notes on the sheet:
How to use JP1, a note on grounding & shielding: For prototyping/breadboarding, the entire board is grounded through the output connector (J4). In that case, leave JP1 intact. If installing in a metal enclosure, the enclosure should be tied to earth, and the shield should be tied to the enclosure a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
This board requires bipolar power, in the range from +/-5VDC to +/-20VDC.
V10
D1, D2, D3, D4 form extended range clamp, holding input to 12V beyond the supply rails. The max Vin range published for the IC is +/-31V.
Chassis ground region
Circuit ground region
Byron Jacquot
J3, J4, J5 are normals of TRS connections. If jack is not present, they connect to their respective T/R/S connections. If jack is present, they float.

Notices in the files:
projects/sparkfun_sunnybuddy/version_current/working/working.kicad_sch:
http://creativecommons.org/licenses/by-sa/3.0
Released under the Creative Commons
projects/sparkfun_teensy_arduino_shield_adapter/version_current/working/working.kicad_sch:
https://creativecommons.org/licenses/by-sa/4.0
parts and their libraries:
Released under the Creative Commons Attribution Share-Alike 4.0 License
Released under the Creative Commons Attribution Share-Alike 3.0 License
